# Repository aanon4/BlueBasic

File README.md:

BlueBasic
=========

**NOTE: I no longer have access to either hardware or tools to update the builds.**

**ALSO NOTE: This project has moved to https://gitlab.com/timwilkinson/BlueBasic**

BASIC interpreter for CC2540 and CC2541 Bluetooth LE chips.

This project contains a BASIC interpreter which can be flashed onto a CC2540 or CC2541 Bluetooth module. Once installed, simple use the Bluetooth Console tool to connect and start coding on the device using good old BASIC.

The project was inspired by experimenting with the HM-10 modules (a cheap BLE module) and a need to provide an easy way to prototype ideas (rather than coding in C using the very expensive IAR compiler). Hopefully other will find this useful.

For more information see https://github.com/aanon4/BlueBasic/wiki/Blue-Basic:-An-Introduction

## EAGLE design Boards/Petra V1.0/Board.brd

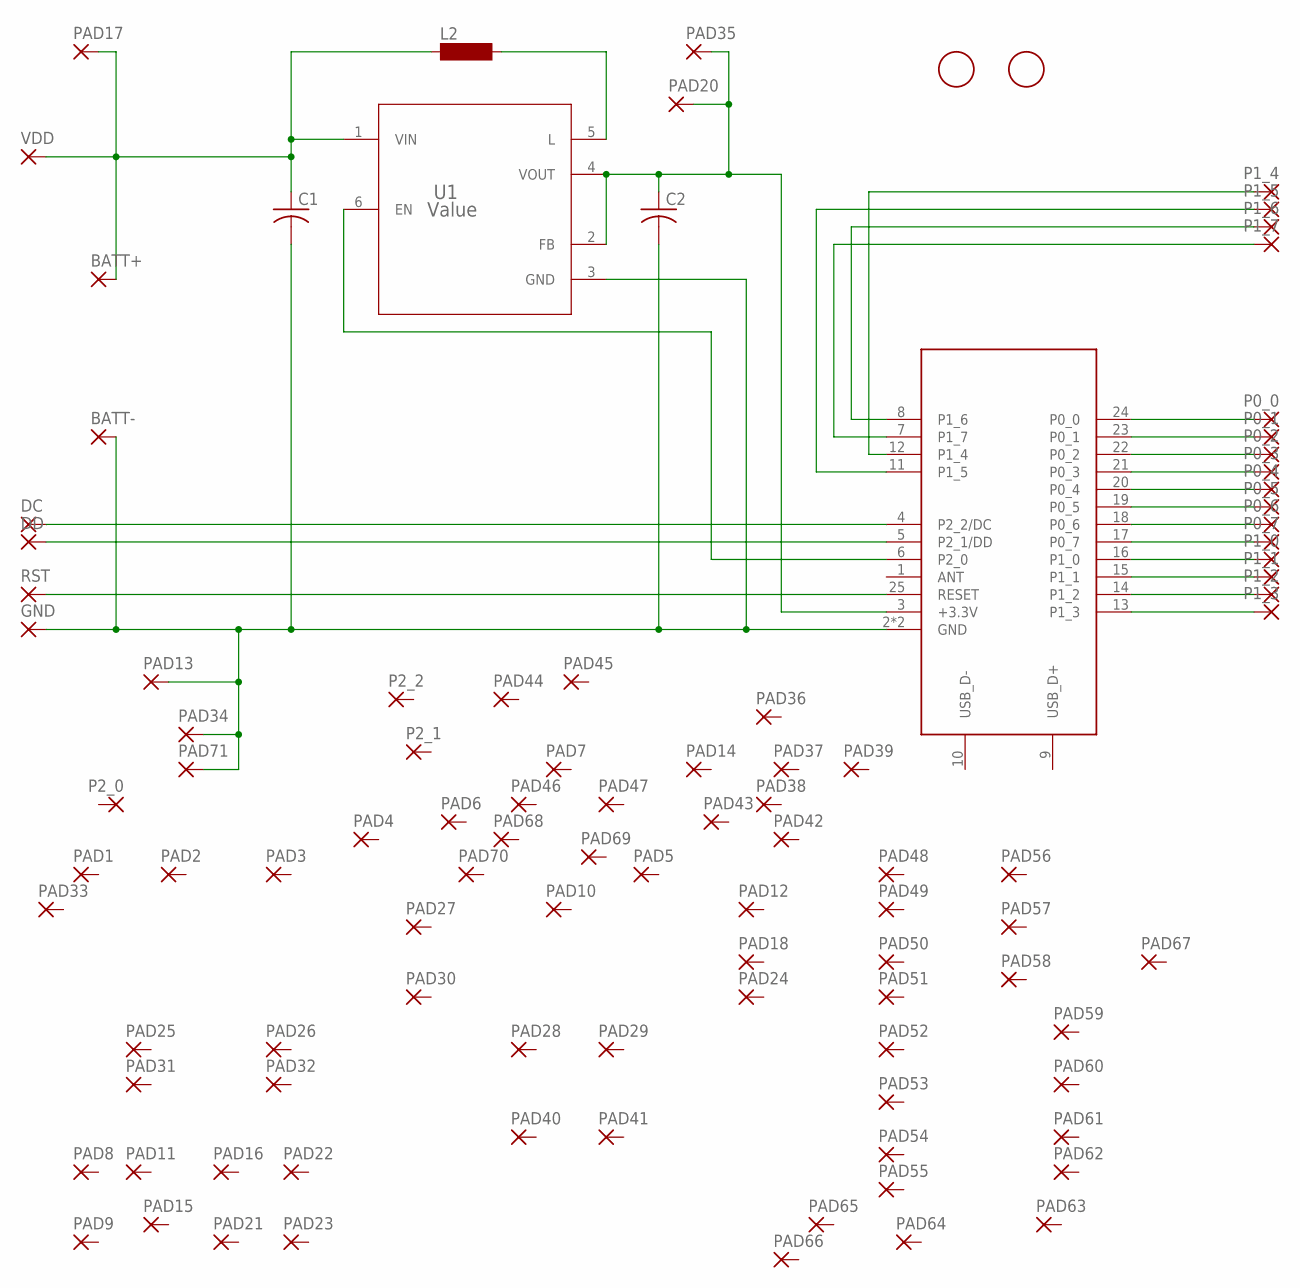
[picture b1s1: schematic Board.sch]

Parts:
BATT+: 1,6/0,9
BATT-: 1,6/0,9
C1, C2: C-USC0603; C0603
DC: SMD2; SMD1,27-2,54
DD: SMD2; SMD1,27-2,54
E1: CC2540-MODULE-BOARD; 24X15_BOARD
GND: SMD2; SMD1,27-2,54
L2: SM-NE29
P0_0, P0_1, P0_2, P0_3, P0_4, P0_5, P0_6, P0_7, P1_0, P1_1, P1_2, P1_3, P1_4, P1_5, P1_6, P1_7, P2_0, P2_1, P2_2: 1,6/0,9
PAD1, PAD2, PAD3, PAD4, PAD5, PAD6, PAD7, PAD8, PAD9, PAD10, PAD11, PAD12, PAD13, PAD14, PAD15, PAD16, PAD17, PAD18, PAD20, PAD21, PAD22, PAD23, PAD24, PAD25, PAD26, PAD27, PAD28, PAD29, PAD30, PAD31, PAD32, PAD33, PAD34, PAD35, PAD36, PAD37, PAD38, PAD39, PAD40, PAD41, PAD42, PAD43, PAD44, PAD45, PAD46, PAD47, PAD48, PAD49, PAD50, PAD51, PAD52, PAD53, PAD54, PAD55, PAD56, PAD57, PAD58, PAD59, PAD60, PAD61, PAD62, PAD63, PAD64, PAD65, PAD66, PAD67, PAD68, PAD69, PAD70, PAD71: 1,6/0,9
RST: SMD2; SMD1,27-2,54
U1: Value; DCK0006A
U$1, U$2: FIDUCIAL; FIDUCIAL_1MM
VDD: SMD2; SMD1,27-2,54

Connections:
3V3: C2.1, E1.3 (+3.3V), PAD20.1, PAD35.1, U1.2 (FB), U1.4 (VOUT)
DC: DC.1, E1.4 (P2_2/DC)
DD: DD.1, E1.5 (P2_1/DD)
GND: BATT-.1, C1.2, C2.2, E1.2 (GND), E1.26 (GND), GND.1, PAD13.1, PAD34.1, PAD71.1, U1.3 (GND)
unnamed: E1.18 (P0_6), P0_6.1
unnamed: E1.17 (P0_7), P0_7.1
unnamed: E1.13 (P1_3), P1_3.1
unnamed: E1.14 (P1_2), P1_2.1
unnamed: E1.15 (P1_1), P1_1.1
unnamed: E1.21 (P0_3), P0_3.1
unnamed: E1.20 (P0_4), P0_4.1
unnamed: E1.19 (P0_5), P0_5.1
unnamed: E1.16 (P1_0), P1_0.1
unnamed: E1.7 (P1_7), P1_7.1
unnamed: E1.8 (P1_6), P1_6.1
unnamed: E1.11 (P1_5), P1_5.1
unnamed: E1.12 (P1_4), P1_4.1
unnamed: E1.6 (P2_0), U1.6 (EN)
unnamed: E1.22 (P0_2), P0_2.1
unnamed: L2.2, U1.5 (L)
P0_0: E1.24 (P0_0), P0_0.1
P0_1: E1.23 (P0_1), P0_1.1
RST: E1.25 (RESET), RST.1
VDD: BATT+.1, C1.1, L2.1, PAD17.1, U1.1 (VIN), VDD.1

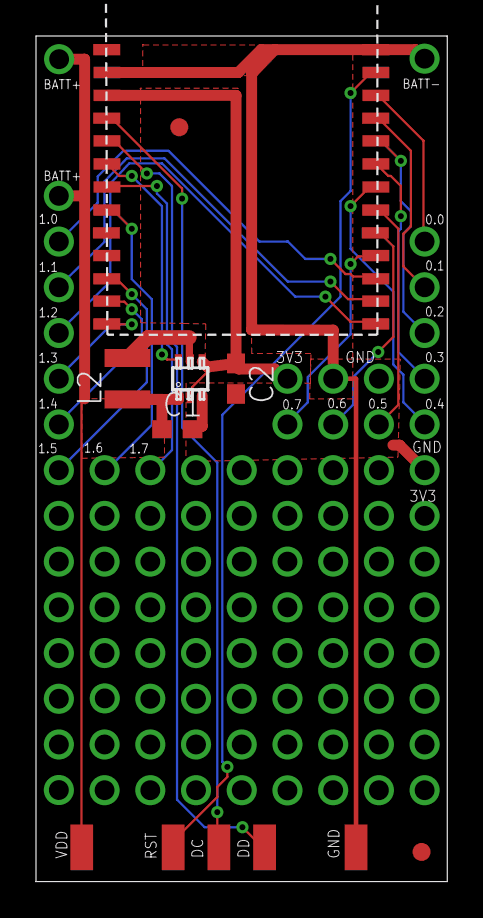
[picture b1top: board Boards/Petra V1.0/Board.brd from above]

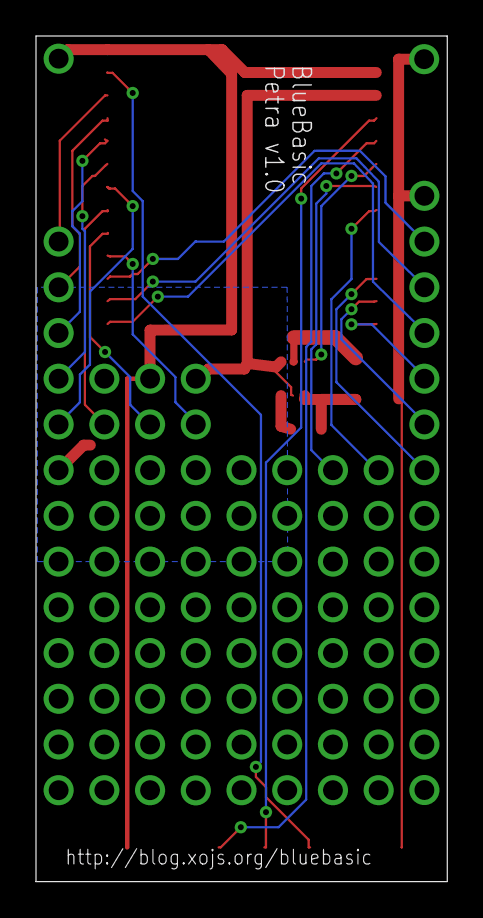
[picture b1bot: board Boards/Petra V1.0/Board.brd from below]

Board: 2 copper layers, 22.8 x 47.0 mm, 103 parts (2 on the bottom side), 24 nets.

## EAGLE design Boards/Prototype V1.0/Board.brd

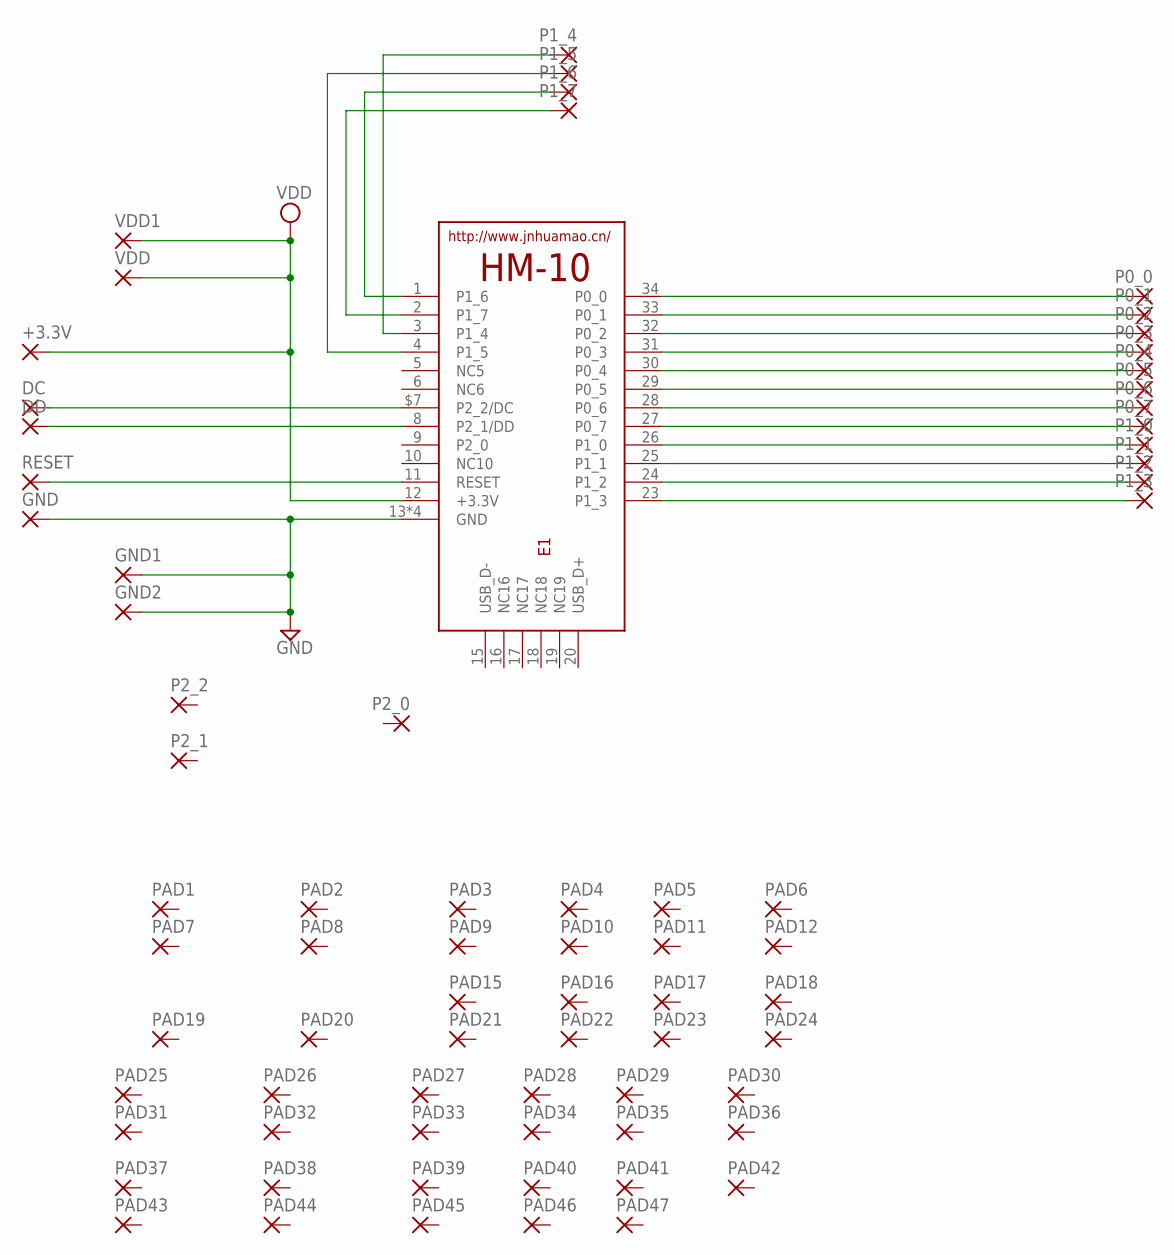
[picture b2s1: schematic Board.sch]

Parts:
+3.3V: SMD2; SMD1,27-2,54
DC: SMD2; SMD1,27-2,54
DD: SMD2; SMD1,27-2,54
E1: HM-10-BOARD; 26.9X13X2.2_BOARD
GND: SMD2; SMD1,27-2,54
GND1, GND2: 1,6/0,9
P0_0, P0_1, P0_2, P0_3, P0_4, P0_5, P0_6, P0_7, P1_0, P1_1, P1_2, P1_3, P1_4, P1_5, P1_6, P1_7, P2_0, P2_1, P2_2: 1,6/0,9
PAD1, PAD2, PAD3, PAD4, PAD5, PAD6, PAD7, PAD8, PAD9, PAD10, PAD11, PAD12, PAD15, PAD16, PAD17, PAD18, PAD19, PAD20, PAD21, PAD22, PAD23, PAD24, PAD25, PAD26, PAD27, PAD28, PAD29, PAD30, PAD31, PAD32, PAD33, PAD34, PAD35, PAD36, PAD37, PAD38, PAD39, PAD40, PAD41, PAD42, PAD43, PAD44, PAD45, PAD46, PAD47: 1,6/0,9
RESET: SMD2; SMD1,27-2,54
VDD, VDD1: 1,6/0,9

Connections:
GND: E1.13 (GND), E1.14 (GND), E1.21 (GND), E1.22 (GND), GND.1, GND1.1, GND2.1
unnamed: E1.28 (P0_6), P0_6.1
unnamed: E1.27 (P0_7), P0_7.1
unnamed: E1.11 (RESET), RESET.1
unnamed: DC.1, E1.$7 (P2_2/DC)
unnamed: DD.1, E1.8 (P2_1/DD)
unnamed: E1.23 (P1_3), P1_3.1
unnamed: E1.24 (P1_2), P1_2.1
unnamed: E1.25 (P1_1), P1_1.1
unnamed: E1.31 (P0_3), P0_3.1
unnamed: E1.30 (P0_4), P0_4.1
unnamed: E1.29 (P0_5), P0_5.1
unnamed: E1.26 (P1_0), P1_0.1
unnamed: E1.2 (P1_7), P1_7.1
unnamed: E1.1 (P1_6), P1_6.1
unnamed: E1.4 (P1_5), P1_5.1
unnamed: E1.3 (P1_4), P1_4.1
unnamed: E1.32 (P0_2), P0_2.1
P0_0: E1.34 (P0_0), P0_0.1
P0_1: E1.33 (P0_1), P0_1.1
VDD: +3.3V.1, E1.12 (+3.3V), VDD.1, VDD1.1

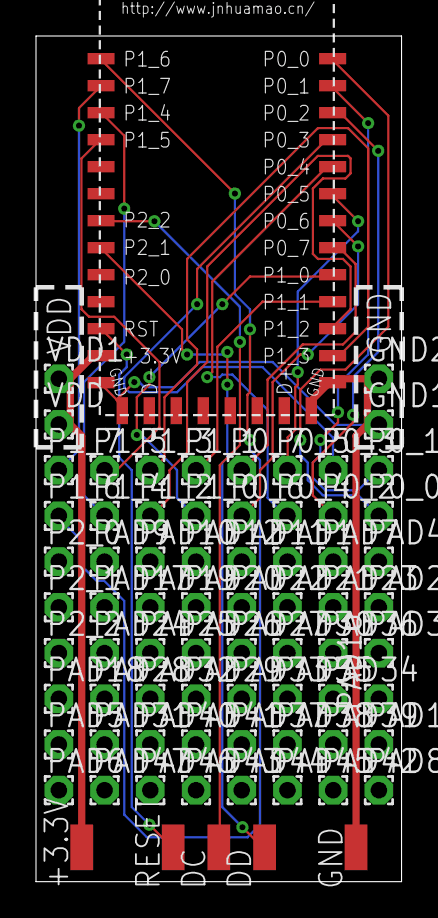
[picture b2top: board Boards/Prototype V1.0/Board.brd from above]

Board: 2 copper layers, 20.3 x 47.0 mm, 74 parts (0 on the bottom side), 21 nets.

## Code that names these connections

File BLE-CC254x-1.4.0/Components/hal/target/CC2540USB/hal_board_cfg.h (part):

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
/* 1 - Green */
#define LED1_BV                        BV(0)
#define LED1_SBIT                      P0_0
#define LED1_DDR                       P0DIR
#define LED1_POLARITY                  ACTIVE_LOW

/* 2 - Red */
#define LED2_BV                        BV(1)
#define LED2_SBIT                      P1_1
#define LED2_DDR                       P1DIR
#define LED2_POLARITY                  ACTIVE_HIGH

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
/* S1 */
#define PUSH1_BV                       BV(2)
#define PUSH1_SBIT                     P1_2
#define PUSH1_POLARITY                 ACTIVE_LOW

/* S2 */
#define PUSH2_BV                       BV(3)
#define PUSH2_SBIT                     P1_3
#define PUSH2_POLARITY                 ACTIVE_LOW

/* OSAL NV implemented by internal flash pages. */
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
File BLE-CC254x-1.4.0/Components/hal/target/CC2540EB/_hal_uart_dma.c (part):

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#define PxIEN                      P0IEN
#define PxIFG                      P0IFG
#define PxIF                       P0IF
#define DMA_RDYIn                  P0_4
#define DMA_RDYOut                 P0_5
#define DMA_RDYIn_BIT              BV(4)        // Same as the I/O Select for CTS flow control.
#define DMA_RDYOut_BIT             BV(5)        // Same as the I/O Select for manual RTS flow ctrl.
// Falling edge ISR on P0 pins.
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#define PxIEN                      P1IEN
#define PxIFG                      P1IFG
#define PxIF                       P1IF
#define DMA_RDYIn                  P1_4
#define DMA_RDYOut                 P1_5
#define DMA_RDYIn_BIT              BV(4)        // Same as the I/O Select for CTS flow control.
#define DMA_RDYOut_BIT             BV(5)        // Same as the I/O Select for manual RTS flow ctrl.
// Falling edge ISR on P1.4-7 pins.
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
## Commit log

2014-08-03 Initial import (v0.2)
    Initial import of BASIC interpreter for the TI CC2540 and CC2541
    Bluetooth LE
2014-08-03 Remove tmp file
2014-08-03 Increase MEM size
2014-08-03 Add prebuilt hex files
2014-08-03 Ignore some paths
2014-08-04 Added post build actions to copy HEX files.
2014-08-04 Battery and Temp measuring functions.
2014-08-04 More to ignore
2014-08-04 Disable TEMP() until calibration if fixed.
2014-08-04 Fix tokenizer for use of "("
2014-08-05 Remove the ENABLE_BLE and ENABLE_PINS defines
    Because they always will be.
2014-08-05 Tidying
2014-08-05 Update gitignore
2014-08-05 Remove double init of non-volatile memory system
2014-08-05 First cut as SPI master support (untested)
2014-08-05 More ignores.
2014-08-05 Unified pin handling
2014-08-05 Analog reference and resolution
2014-08-06 New more efficient tokenizer.
2014-08-06 Remove STOP (alias for END)
2014-08-06 Formatting
2014-08-06 Remove GAP Bond Manager profile by default
2014-08-06 Update HEX
2014-08-07 Add TXPOWER and RXGAIN
2014-08-07 Added OBSERVER abilities - can scan for devices
2014-08-07 Updated HEX
2014-08-08 Block re-entry into console code.
2014-08-08 Simple SPI test
2014-08-10 Unify getting/setting various BT params
2014-08-11 Separate constants from keywords
    Want lots of constant and we’d run out of keyword space without this.
2014-08-11 Provide RSSI info during a connection
2014-08-12 Fix ADC option for PINMODE
2014-08-12 Keyword update
2014-08-12 Syntax fix
2014-08-13 Improve discovery and I/O
2014-08-13 Keep advertising (rather than stopping at 30s)
2014-08-13 Added MASTER keyword to SPI setup
2014-08-13 Added DELAYMICROSECONDS
2014-08-13 Fix MILLIS()
2014-08-13 New tests
2014-08-13 Optimize dispatch loop (on-going)
2014-08-13 Remove 'current_line'
    Managing current line is generally not useful and just increases the
    time
    in the dispatch loop.
2014-08-13 Trivial loop optimizations
2014-08-14 PULSEIN function
2014-08-15 Replaced expression evaluator
    Replaced expression evaluator with something non-recursive.
2014-08-15 WIRE command
    The WIRE command executes a series of commands on a pin (or pins) in
    order.
    This is useful for running a protocol to an external device where
    timing is important.
2014-08-15 Fix quote overflow bug.
2014-08-15 More WIRE. More expression
    Improved WIRE command
    Increased complexity of expression evaluations + added << and >>
2014-08-15 Rewrite flash store
    Flash store isn’t as flexible as it appears. Modify code to make it
    work.
    To be honest, this isn’t going to work long term, so will need to write
    a new flash store
    manager.
2014-08-15 Support WAITs during WIRE commands
2014-08-15 shift rather than divide
2014-08-17 I2C support
2014-08-18 Deprecated FI and reuse END
    Now use END to finish conditions: e.g. IF … ELSE … END
    No longer use END to terminate a program (unstructured), but can use
    RETURN to return
    from main entry point.
2014-08-18 Fix indenting
2014-08-18 Remove pin_write
2014-08-18 Fix example
2014-08-18 Remove DELAYMICROSECONDS
    This is a rather non-sensical operation in an interpreter which really
    doesn’t let you
    manage microsecond delays. Usually used for managing delays when
    running wire protocols,
    so better to use the WIRE command.
2014-08-18 Add ADC reading into WIRE
2014-08-19 Fix ADC and multiline WIREs
2014-08-19 V0.3
2014-08-20 Support multi-line WIREs. Kill LET keyword
2014-08-21 More WIRE optimizations
2014-08-22 CC2541 config fixes.
2014-08-22 Generate more unique default names: BASIC#??
2014-08-22 Use low byte in name, not high.
2014-08-22 No 4dBm mode for CC2541
2014-08-23 Don't include UART pin exception for BLE console
2014-08-30 I2C fixes
2014-08-30 Improved I2C syntax
    Also fixed a few other bugs.
2014-08-30 Improved default setup and avoid setup calls.
2014-08-30 i2c test
2014-08-30 Support I2C write then read syntax
2014-08-31 New Hex
2014-08-31 More tests
2014-08-31 Rebuild console system for better performance
2014-08-31 Shutdown console on disconnect
2014-09-01 Trim a few more unnecessary function calls.
2014-09-02 Merged CC2540 and CC2541 configs
2014-09-02 Import BIM
2014-09-03 Fix libraries
2014-09-03 ImgB support
2014-09-03 ImgA + ImgB linker defs
2014-09-03 BIM image size changes
2014-09-03 BlueBasicLoader ImgA
    Minimal BLE build used to OTA BlueBasic firmware
2014-09-04 Speed up firmware uploads
2014-09-04 REBOOT can invalidate ImgB so we can update
2014-09-04 Better firmware versioning
2014-09-05 Display more version info.
2014-09-05 Put back accidentally removed os.h
2014-09-05 Update configs
2014-09-05 v0.4
2014-09-05 Import OSX Console source into main git repo
2014-09-06 Better timestamps
2014-09-06 Hex images are now OAD upgradable
2014-09-06 Full updates for CC2540 and CC2541
2014-09-06 Add a few examples
2014-09-08 Flash code store (WIP)
2014-09-09 Flash based programs.
2014-09-09 CC2540 has a ~4K NanoRiscImage. Reuse Loaders. This takes up more space than I'd like so rather than keep it in the ImgB we reuse it from ImgA (the Loader) which will be constant. Not ideal.
2014-09-09 More flash work
    Strip DLOAD/DSAVE (temp)
    Remove OSAL_NV system (no longer used)
    Add SPECIALs
2014-09-09 V0.5
2014-09-10 Data store/file system
    OPEN, READ, WRITE, EOF, CLOSE
2014-09-10 26 files (A-Z), 4 open at once
2014-09-10 Flash wear leveling during allocation
2014-09-10 Hex.
2014-09-10 Unsigned (typo of the brain!)
2014-09-11 Switch to LIMITED discoverable mode by default
    Also add a few more constants to help configure this stuff.
2014-09-15 Added V1 and V1.1 boards
2014-09-15 Added console package
2014-09-15 Switch to zipped app
    Cant get the code signing working for installer package, do distribute
    like this until that’s sorted.
2014-09-16 Add some keyword spacers
    The spacers allow me to add new keywords later on without renumbering
    things.
2014-09-16 Support boost converter (hardware v1.1)
2014-09-16 Slight tweaks to INTERRUPT setup/teardown
2014-09-16 Serial port support
2014-09-19 Tidied up file system apis
2014-09-19 Use true lengths in flash items
    Use true lengths in flash items, rather than rounding them up to 4 byte
    boundaries. The flash items are still rounded up, but we store the
    actual length.
2014-09-19 Put port param back in OS_serial_<func>
    Only support one port at the moment, but put the param back for later
    (maybe).
2014-09-19 Added URL for more info
2014-09-21 Serial changes
    Move serial handling into main event loop.
    Support CLOSE SERIAL
2014-09-21 Remove file "records" - byte streams are better!
    Note. We cannot hang onto any references to the flash between read
    calls because it may get compacted, invalidating these references.
2014-09-22 Increase number of writes a file can support.
2014-09-22 Simplify ONREAD/ONWRITE serial callbacks
2014-09-22 Fix autorun.
2014-09-22 A couple of simple file system tests.
2014-09-22 Fix file appends (+test)
2014-09-27 iBeacon example
2014-09-27 Set initial name in GATT
2014-09-27 Add fake OAD profile so we match the loader
2014-09-27 Move old console program aside
2014-09-27 New console version (Swift code)
2014-09-27 Update pre-built console
2014-09-30 Fixed old console so it will still connect
2014-09-30 Improve firmware upgrade speed by quite a bit
2014-10-01 Add simple lower power setup example
2014-10-01 Remove some dead code
2014-10-01 Allow milliseconds to be set
    Can now set the millisecond clock to a base time. This lets us sync it
    to a remote clock (minus some base epoch).
2014-10-01 Unused code
2014-10-01 Fix iBeacon example
2014-10-01 Flip major+minor number setup to make it more obvious
2014-10-01 Move example
2014-10-01 Support name updates
2014-10-01 Updated console binary
2014-10-02 Move bluetooth configs onto heap
    Now the program is in Flash, it is possible to have a heap as well as a
    stack.
    Moving the bluetooth config onto the heap means it can now be created
    inside subroutines and will persist after they return. This is more
    sane and obvious.
2014-10-02 Update app
    Xcode will now build production version without crashing.
2014-10-02 A little more selective with cache invalidation
2014-10-02 Fix warning
2014-10-02 DevMfrName == BlueBasic info URL
2014-10-03 Strip ( from functions
    Simplifies the expression parser if we don’t include a ( in the token
    name. Also let the keywords be reused for non-function purposes.
2014-10-03 Allow ports to be excluded from builds.
2014-10-03 More expression tweaking
2014-10-03 Rename BTSET to BTPOKE
    And BTGET to BTPEEK .. which seems a bit more BASICy
2014-10-03 Count values inside (...) for better error handling
2014-10-03 Added Petra build
2014-10-03 OSX Bluetooth reload utility
    OSX aggressively caches bluetooth services and characteristics but
    provides no programatic way to clear this information when the device
    changes. This utility will flush the cache and force a reload.
2014-10-06 Added iPhone & iPad builds for Console
    Basic version of iPhone and iPad consoles. You can choose a device,
    connect and type. No uploads or firmware updates yet. Rotation still
    needs work.
    Lots of common code between iOS and OSX version.
2014-10-06 Fix keyboard/text sizing when rotating
2014-10-06 Fix bug where device not disconnecting
2014-10-06 Manage the Device popover
2014-10-07 Rename images
2014-10-07 Fix disconnect on iPhone
2014-10-07 Bug fix serial port
    Serial only works reliably if you use hardware handshaking. So this is
    now a requirement.
2014-10-07 Add pullToRefresh to refresh scanned devices
2014-10-08 Added RSSI indicators
2014-10-08 Added build versions to Hex directory
    Build versions are part of the auto-update feature coming soon.
2014-10-08 Support auto-update of firmware on OSX
2014-10-09 Auto-upgrade support in iOS
2014-10-09 Add serial/usart demo example
2014-10-09 Recovery mode for hosed devices
2014-10-09 Include devinfo in loader
    Include basic devinfo in the loader so we can recover from failed
    upgrades.
2014-10-09 New example
2014-10-15 Make I2C pull-ups optional (to allow for external pull-ups)
2014-10-15 Update I2C example
2014-10-17 Fix pinmode adc bug
2014-10-17 Extra SPI parameter to allow chip select to toggle
    An optional SPI MASTER parameter will toggle the CS bit every 8, 16 or
    32 bits of transfer (for devices that like this sort of thing).
2014-10-17 Stop timers when program modified
2014-10-22 Support simplified array assignment
2014-10-22 Xcode changes for submission to stores
2014-10-23 Fix SPI bug
2014-10-23 Update examples
2014-10-23 Fix *both* SPI ports (sigh)
2014-10-25 Optimize array variable access
2014-10-28 Support closing incoming connections
    GATT CLOSE can be use to close incoming connections.
2014-10-29 Exclude a few more port2 pins.
    P2_3 and P2_4 are use for the low frequently clock.
2014-10-30 Add final Petra board
2014-11-03 Rename BlueBasicConsole OSX version to BlueBasicOSX
2014-11-09 Add bonding manager
2014-11-09 More MacStore rule tweaks
2014-11-09 Add bond manager back in for all configs
2014-11-10 Add constants to set passcode and enable bonding
2014-11-10 Remove unused test projects
2014-11-10 Now error for bad btpeeks
2014-11-10 Allow creation of authenticated services
2014-12-03 Fix TXPOWER
2014-12-03 Update example
2014-12-03 Update build name for Mac AppStore
2014-12-03 Bump version nr.
2014-12-06 Tool upgrade
2015-01-05 Add space for extended variable in service
    Forgot to allow space for extended variable when used as part of a
    service. Was corrupting heap.
2015-01-05 Increase stack size
2015-02-07 Fix multi-byte i2c reads
2015-02-07 Project upgraded to IAR 9.10.1
2015-02-07 DELAY -1 will pause forever
2015-02-13 Fix command hang are using AUTORUN ON
2015-02-22 Access all P2 pins
    Allow access to all P2 pins in the non-Petra builds.
2015-05-27 Fix INTERRUPTs
2015-05-27 Rename
2015-05-27 Compiler config update
2015-05-28 Car beacon example
2015-06-07 Fix bad default settings for some output pins.

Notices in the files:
BLE-CC254x-1.4.0/Components/hal/target/CC2540EB/_hal_uart_dma.c:
Copyright 2006-2013 Texas Instruments Incorporated. All rights reserved.
granted under the terms of a software license agreement between the user
BLE-CC254x-1.4.0/Components/hal/target/CC2540USB/hal_board_cfg.h:
Copyright 2009-2012 Texas Instruments Incorporated. All rights reserved.
